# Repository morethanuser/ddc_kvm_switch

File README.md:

# ddc_kvm_switch
Software and hardware for  ddc kvm swtich

More info at: http://morethanuser.blogspot.com/2018/03/ddc-i2c-kvm-with-mouse-keyboard.html

YouTube demo: https://www.youtube.com/watch?v=Knsj12kxSOc

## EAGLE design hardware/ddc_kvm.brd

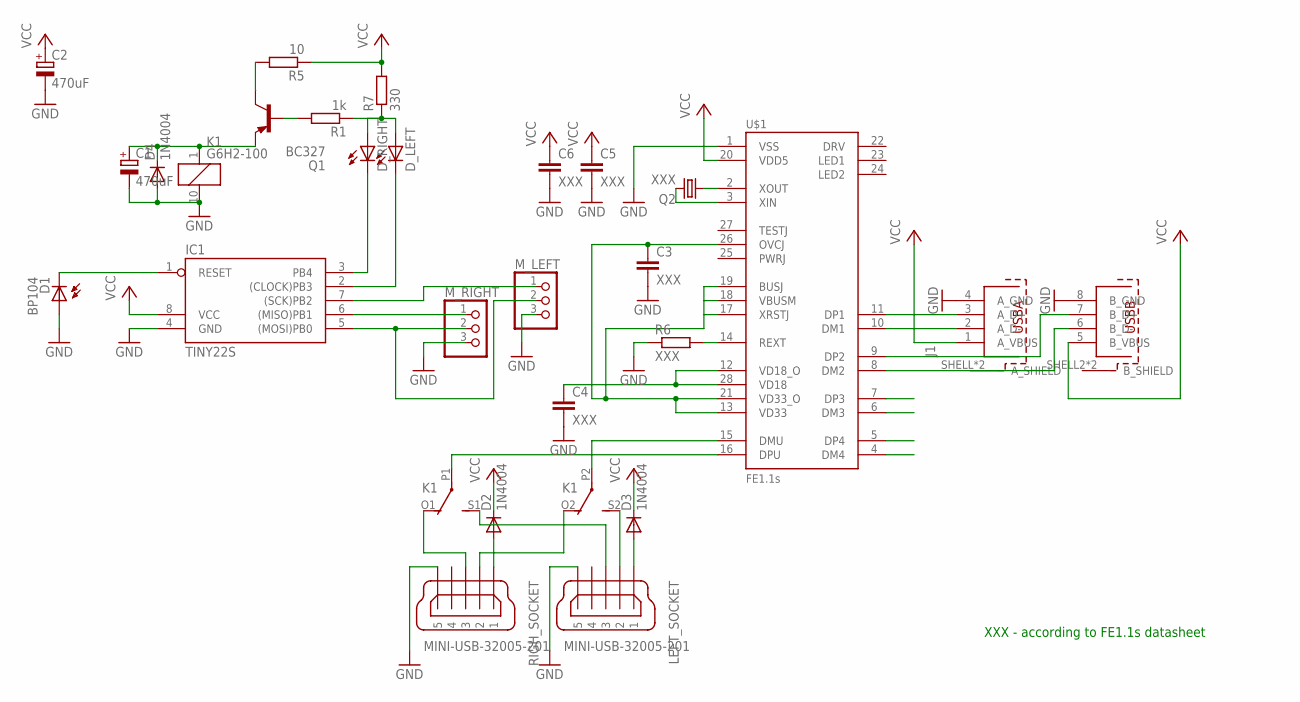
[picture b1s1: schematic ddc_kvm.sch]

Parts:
C1: 470uF; E3,5-8
C2: 470uF; E3,5-10
C3, C4, C5, C6: XXX; C0603
D1: BP104
D2, D3, D4: 1N4004; DO41-10
D_LEFT: LED5MM
D_RIGHT: LED5MM
IC1: TINY22S; SOIC8
J1: 61400826021
K1: G6H2-100
LEFT_SOCKET: MINI-USB-32005-201; 32005-201
M_LEFT: PINHD-1X3; 1X03
M_RIGHT: PINHD-1X3; 1X03
Q1: BC327; TO92
Q2: XXX; HC49/S
R1: 1k; R0603
R5: 10; 0204V
R6: XXX; R0603
R7: 330; R0603
RIGH_SOCKET: MINI-USB-32005-201; 32005-201
U$1: FE1.1S; FE1.1S_SSOP-28

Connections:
GND: C1.-, C2.-, C3.2, C4.2, C5.2, C6.2, D1.A, D4.A, IC1.4 (GND), J1.4 (A_GND), J1.8 (B_GND), K1.10 (2), LEFT_SOCKET.5, M_LEFT.3, M_RIGHT.3, R6.1, RIGH_SOCKET.5, U$1.1 (VSS)
unnamed: J1.3 (A_D+), U$1.11 (DP1)
unnamed: J1.2 (A_D-), U$1.10 (DM1)
unnamed: J1.7 (B_D+), U$1.9 (DP2)
unnamed: J1.6 (B_D-), U$1.8 (DM2)
unnamed: Q2.1, U$1.2 (XOUT)
unnamed: Q2.2, U$1.3 (XIN)
unnamed: R6.2, U$1.14 (REXT)
unnamed: K1.S2 (S), LEFT_SOCKET.2
unnamed: K1.O1 (O), RIGH_SOCKET.3
unnamed: K1.P2, U$1.15 (DMU)
unnamed: K1.O2 (O), RIGH_SOCKET.2
unnamed: K1.S1 (S), LEFT_SOCKET.3
unnamed: K1.P1, U$1.16 (DPU)
unnamed: D3.A, LEFT_SOCKET.1
unnamed: D2.A, RIGH_SOCKET.1
unnamed: IC1.5 ((MOSI)PB0), M_LEFT.2, M_RIGHT.2
unnamed: D1.K (C), IC1.1 (RESET)
unnamed: IC1.6 ((MISO)PB1), M_RIGHT.1
unnamed: IC1.7 ((SCK)PB2), M_LEFT.1
unnamed: Q1.3 (C), R5.2
unnamed: D_RIGHT.K (C), IC1.3 (PB4)
unnamed: D_LEFT.K (C), IC1.2 ((CLOCK)PB3)
unnamed: D_LEFT.A, D_RIGHT.A, R1.1, R7.1
unnamed: Q1.2 (B), R1.2
unnamed: C1.+, D4.C, K1.1, Q1.1 (E)
unnamed: C3.1, U$1.13 (VD33), U$1.17 (XRSTJ), U$1.18 (VBUSM), U$1.19 (BUSJ), U$1.21 (VD33_O), U$1.26 (OVCJ)
unnamed: C4.1, U$1.12 (VD18_O), U$1.28 (VD18)
VCC: C2.+, C5.1, C6.1, D2.C, D3.C, IC1.8 (VCC), J1.1 (A_VBUS), J1.5 (B_VBUS), R5.1, R7.2, U$1.20 (VDD5)

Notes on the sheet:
XXX - according to FE1.1s datasheet

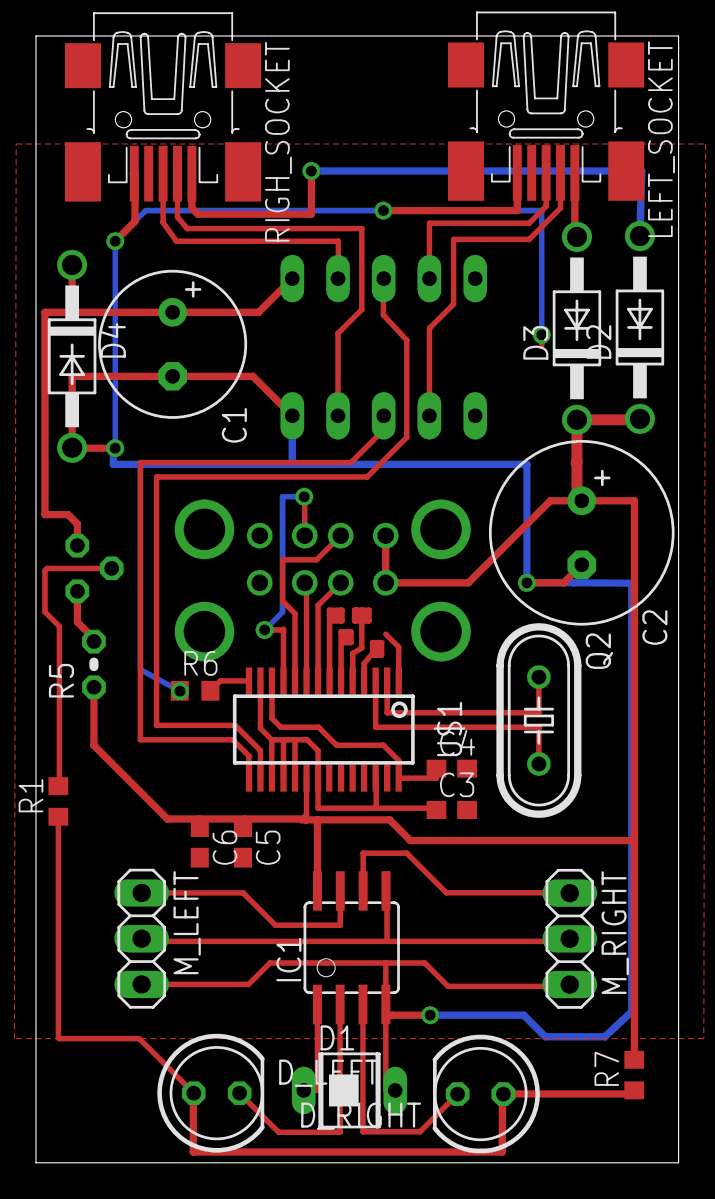
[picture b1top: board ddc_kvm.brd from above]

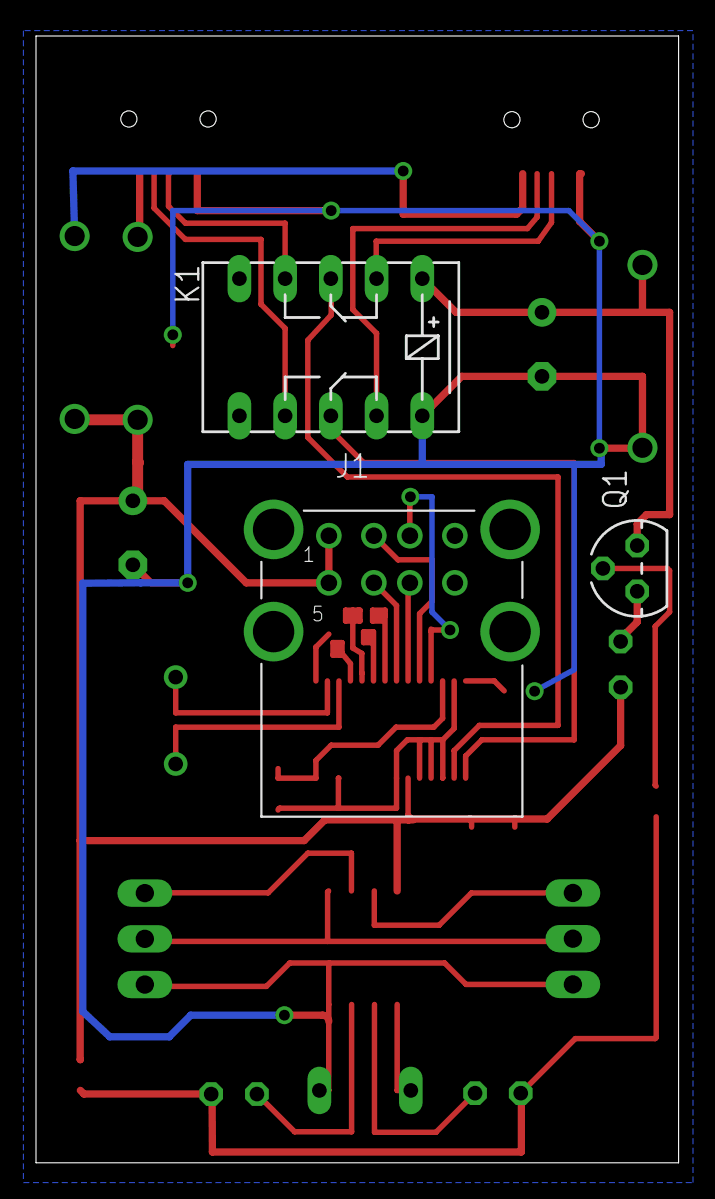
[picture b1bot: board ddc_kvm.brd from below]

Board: 2 copper layers, 35.7 x 62.6 mm, 26 parts (3 on the bottom side), 29 nets.

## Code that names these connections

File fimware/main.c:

/****************************************************************************/
/* Author: hardware.coder@gmail.com                                         */
/* https://github.com/morethanuser/ddc_kvm_switch                           */
/* http://morethanuser.blogspot.com                                         */
/****************************************************************************/
#include "main.h"

#include <avr/io.h>
#include <util/delay.h>
#include <stdlib.h>

// lines to monior DDC
#define SDA_LEFT  PB2
#define SDA_RIGHT PB1
#define SCL       PB0

// IR led drivers
#define LEFT  PB3
#define RIGHT PB4

// ADC threshold
#define THRESHOLD 0x1F

// payloads
const uint8_t analog[] = {0x6E, 0x51, 0x84, 0x03, 0x60, 0x00, 0x01, 0xd9};
const uint8_t dvi[]    = {0x6E, 0x51, 0x84, 0x03, 0x60, 0x00, 0x03, 0xdb};
const uint8_t hdmi[]   = {0x6E, 0x51, 0x84, 0x03, 0x60, 0x00, 0x11, 0xc9};

// length of above commands
#define CMD_LENGTH 8


/****************************************************************************/
/* Function for bit-banging byte data on two I2C SDA lines at the same time.*/
/****************************************************************************/
void byte(uint8_t left, uint8_t right) {
   uint8_t i=7;

   H(DDRB, SDA_LEFT);
   H(DDRB, SDA_RIGHT);

   do {
      if (left & (1 << i)) {
         H(PORTB, SDA_LEFT);
      } else {
         L(PORTB, SDA_LEFT);
      }

      if (right & (1 << i)) {
         H(PORTB, SDA_RIGHT);
      } else {
         L(PORTB, SDA_RIGHT);
      }

      _delay_us(5);

      H(PORTB, SCL);
      _delay_us(150);

      L(PORTB, SCL);
      _delay_us(150);
   } while(i--);

   // let slaves pull down SDA
   L(DDRB, SDA_LEFT);
   L(DDRB, SDA_RIGHT);

   // wait for reply
   _delay_us(50);

   // last clk tick
   H(PORTB, SCL);
   _delay_us(150);
   L(PORTB, SCL);

   _delay_ms(1);
   _delay_us(200);
}


/****************************************************************************/
/* Function for sending commands to two monitors at same time.              */
/* One restriction is that length of left and rigth command buffer needs to */
/* be same length.                                                          */
/****************************************************************************/
void cmd(const uint8_t *left, const uint8_t *right, const uint8_t length) {
   uint8_t i = 0;

   H(DDRB, SDA_LEFT);
   H(DDRB, SDA_RIGHT);
   H(DDRB, SCL);

   H(PORTB, SDA_LEFT);
   H(PORTB, SDA_RIGHT);
   H(PORTB, SCL);

   _delay_ms(10);

   // start condition
   L(PORTB, SDA_LEFT);
   L(PORTB, SDA_RIGHT);
   _delay_us(100);

   L(PORTB, SCL);
   _delay_us(150);

   H(PORTB, SDA_LEFT);
   H(PORTB, SDA_RIGHT);

   _delay_ms(2);

   // strat clock data
   for(i=0; i < length; i++)
      byte(left[i], right[i]);

   H(DDRB, SDA_LEFT);
   H(DDRB, SDA_RIGHT);

   // stop condition
   _delay_us(300);
   L(PORTB, SDA_LEFT);
   L(PORTB, SDA_RIGHT);
   _delay_us(150);
   H(PORTB, SCL);
   _delay_us(150);
   H(PORTB, SDA_LEFT);
   H(PORTB, SDA_RIGHT);

   _delay_ms(10);
   L(DDRB, SDA_LEFT);
   L(DDRB, SDA_RIGHT);
   L(DDRB, SCL);
}


/****************************************************************************/
/* General function for getting ADC data.                                   */
/****************************************************************************/
uint16_t get() {

   uint16_t res1 = 0;
   uint16_t res2 = 0;
   uint16_t res3 = 0;

   H(ADCSRA, ADSC);
   while(IS(ADCSRA, ADSC));
   res1 = ADCW;

   H(ADCSRA, ADSC);
   while(IS(ADCSRA, ADSC));
   res2 = ADCW;

   H(ADCSRA, ADSC);
   while(IS(ADCSRA, ADSC));
   res3 = ADCW;

   return (res1 + res2 + res3) / 3;
}


/****************************************************************************/
/* Main with infinite loop.                                                 */
/****************************************************************************/
int main(void) {

   // ADC reference voltage is VCC
   L(ADMUX, REFS0);
   L(ADMUX, REFS1);

   L(ADMUX, ADLAR);
   H(ADCSRA, ADEN);
   H(ADCSRA, ADPS2);

   // setup IR drivers
   H(DDRB, LEFT);
   H(DDRB, RIGHT);

   // disable IR diodes for now
   H(PORTB, LEFT);
   H(PORTB, RIGHT);

   // for detecting IR diode reflections
   uint8_t left  = 0;
   uint8_t right = 0;

   // for saving prev state
   uint8_t left_prev  = 0;
   uint8_t right_prev = 0;

   // delay used to control relay by IR diodes power cycle length
   uint8_t delay = 1;

   uint16_t adc_val = 0;

   while(1) {

      // get base for adc change detection
      adc_val = get();

      // check if left IR reflection hit PIN diode
      L(PORTB, LEFT);
      _delay_us(500);
      if (abs(adc_val - get()) > THRESHOLD)
         left = 1;
      else
         left = 0;
      H(PORTB, LEFT);

      _delay_ms(2);

      // if delay is true, sleep more - feed less power to relay
      if(delay)
         _delay_ms(50);

      // check if right IR reflection hit PIN diode
      L(PORTB, RIGHT);
      _delay_us(500);
      if (abs(adc_val - get()) > THRESHOLD)
         right = 1;
      else
         right = 0;
      H(PORTB, RIGHT);

      if (left != left_prev)
         if (left_prev == 1 && right == 1) {
            // send command to monitors (switch to server displays)
            cmd(dvi, dvi, CMD_LENGTH);
            // disable relay power
            delay = 1;

            // additional delay, because previous loop was shorter
            // due to delay = 0
            _delay_ms(50);
         }

      if (right != right_prev)
         if (left == 1 && right_prev == 1) {
            // send command to monitors (switch to laptop displays)
            cmd(analog, hdmi, CMD_LENGTH);
            // enable relay power
            delay = 0;
         }

      left_prev  = left;
      right_prev = right;
   }

	return 0;
}

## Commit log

2018-03-29 Firmware stuff.
2018-03-29 Hardware stuff.
2018-03-30 Add link.
2018-03-30 Adding YT link.
2018-04-07 Move to dynamic threshold.
    Static threshold was not enough. Sometimes sunlight
    was causing distortions and unplanned swtich.
    Also dos2unix.
2018-04-07 Add aditional delay on left->right swipe.
    Due to delay=0 that is controlling relay power, while
    loop was running faster.
    When switching from delay=0 to delay=1, left IR reflection
    has been triggered faster and this was false-positive to
    switch logic.
2018-04-07 Increasing ADC threshold.
    Smaller one generated false-positives.
2018-04-07 Changing adc settings.

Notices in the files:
parts and their libraries:
InputOutputIO: Copyright: Würth Elektronik
